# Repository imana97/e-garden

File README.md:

## E-garden

Arduino Shield:

PCB Design:

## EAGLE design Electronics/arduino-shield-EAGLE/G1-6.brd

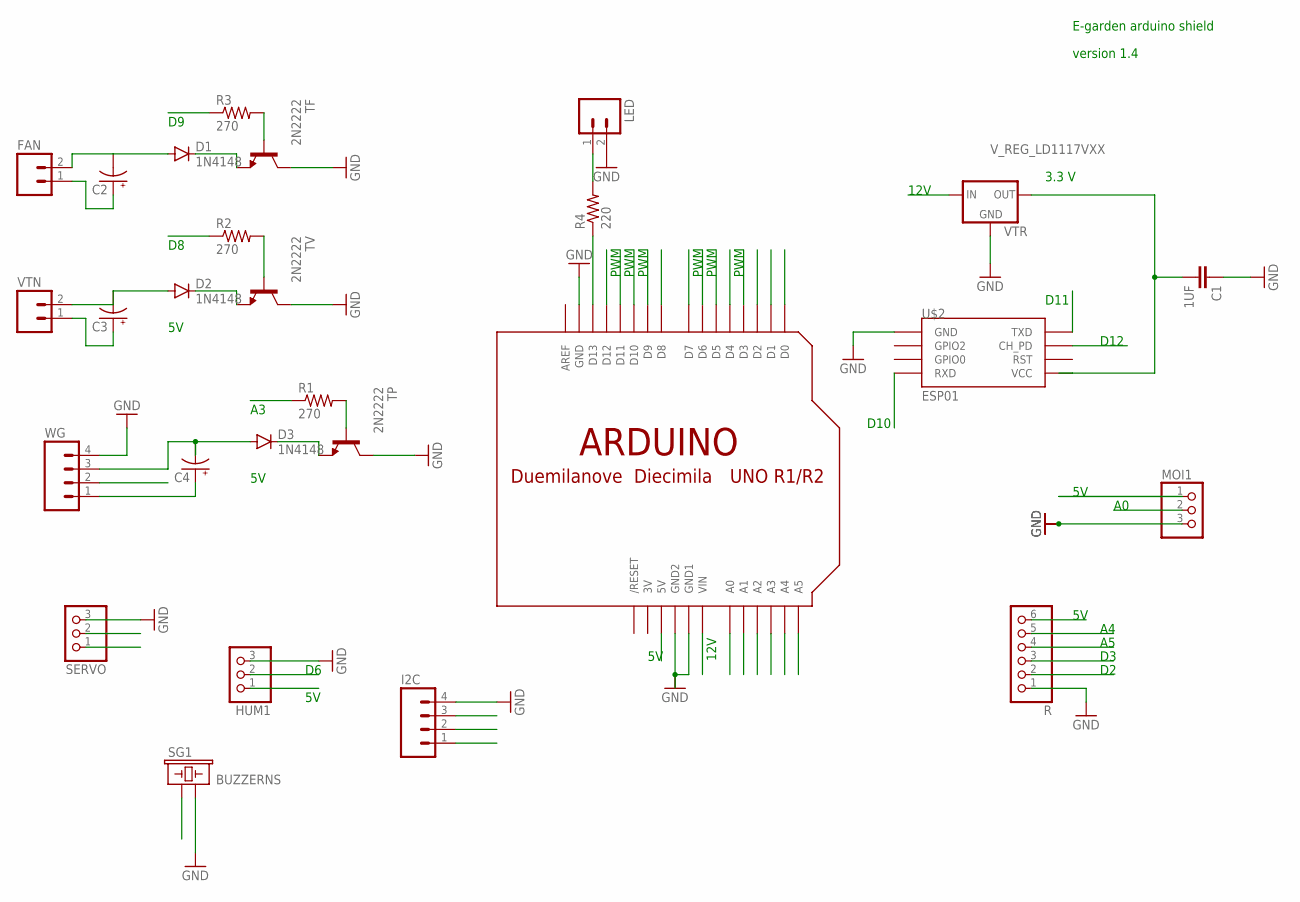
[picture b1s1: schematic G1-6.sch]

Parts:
C1: 1UF; CAP-PTH-SMALL-KIT
C2, C3, C4: CAP_POLPTH2; CPOL-RADIAL-10UF-25V
D1, D2, D3: 1N4148; DIODE-1N4148
FAN: M02PTH; 1X02
HUM1: PINHD-1X3CB; 1X03-CLEANBIG
I2C: M04NO_SILK_ALL_ROUND; 1X04_NO_SILK_ALL_ROUND
LED: M02PTH; 1X02
MOI1: PINHD-1X3CB; 1X03-CLEANBIG
R: PINHD-1X6CB; 1X06-CLEANBIG
R1, R2, R3: 270; AXIAL-0.4
R4: 220; AXIAL-0.4
SERVO: PINHD-1X3CB; 1X03-CLEANBIG
SG1: BUZZERNS; BUZZER-12MM-NS
TF: 2N2222; TO92-EBC-OVAL
TP: 2N2222; TO92-EBC-OVAL
TV: 2N2222; TO92-EBC-OVAL
U$1: ARDUINO-BPLACE
U$2: ESP01
VTN: M02PTH; 1X02
VTR: V_REG_LD1117VXX; 78XXL
WG: M04NO_SILK_ALL_ROUND; 1X04_NO_SILK_ALL_ROUND

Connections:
3V: U$1.3V
A0: MOI1.2, U$1.A0
A1: U$1.A1, WG.2
A2: R.4, U$1.A2
A3: R.5, U$1.A3
A4: I2C.3, U$1.A4
A5: I2C.2, U$1.A5
D0: U$1.D0
D1: U$1.D1
D2: R.3, U$1.D2
D3: R.2, U$1.D3
D4: SERVO.2, U$1.D4
D5: SG1.+ (1), U$1.D5
D6: HUM1.2, U$1.D6
D7: R1.P$1 (1), U$1.D7
D8: R2.P$1 (1), U$1.D8
D9: R3.P$1 (1), U$1.D9
D10: U$1.D10, U$2.RX (RXD)
D11: U$1.D11, U$2.TX (TXD)
D12: U$1.D12, U$2.CH_PD
D13: R4.P$1 (1), U$1.D13
GND: C1.1, HUM1.3, I2C.4, LED.2, MOI1.3, R.1, SERVO.3, SG1.- (2), TF.C, TP.C, TV.C, U$1.GND, U$1.GND1, U$1.GND2, U$2.GND, VTR.IN (GND), WG.4
unnamed: D1.C, TF.E
unnamed: LED.1, R4.P$2 (2)
unnamed: D2.C, TV.E
unnamed: D3.C, TP.E
unnamed: R3.P$2 (2), TF.B
unnamed: C3.2 (-), D2.A, VTN.2
unnamed: R1.P$2 (2), TP.B
unnamed: C1.2, U$2.VCC, VTR.GND (OUT)
unnamed: C2.2 (-), D1.A, FAN.2
unnamed: C4.2 (-), D3.A, WG.3
TV: R2.P$2 (2), TV.B
V5: C2.1 (+), C3.1 (+), C4.1 (+), FAN.1, HUM1.1, I2C.1, MOI1.1, R.6, SERVO.1, U$1.5V, VTN.1, WG.1
V12: U$1.VIN, VTR.OUT (IN)

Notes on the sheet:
12V
3.3 V
D11
D10
D12
E-garden arduino shield
PWM
version 1.4

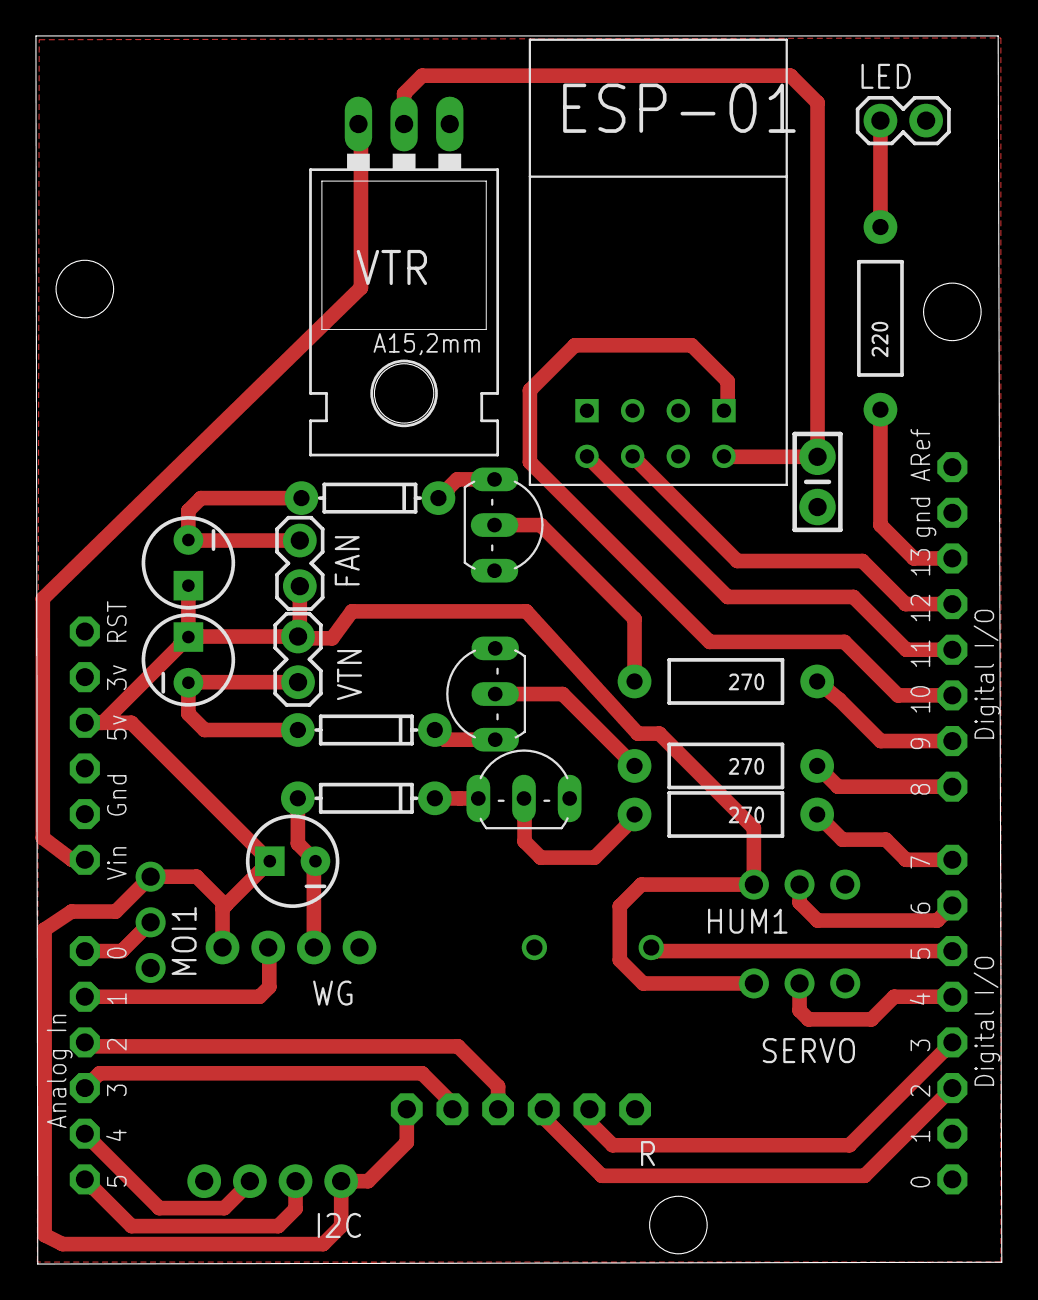
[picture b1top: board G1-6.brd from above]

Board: 2 copper layers, 53.7 x 68.3 mm, 27 parts (0 on the bottom side), 32 nets.

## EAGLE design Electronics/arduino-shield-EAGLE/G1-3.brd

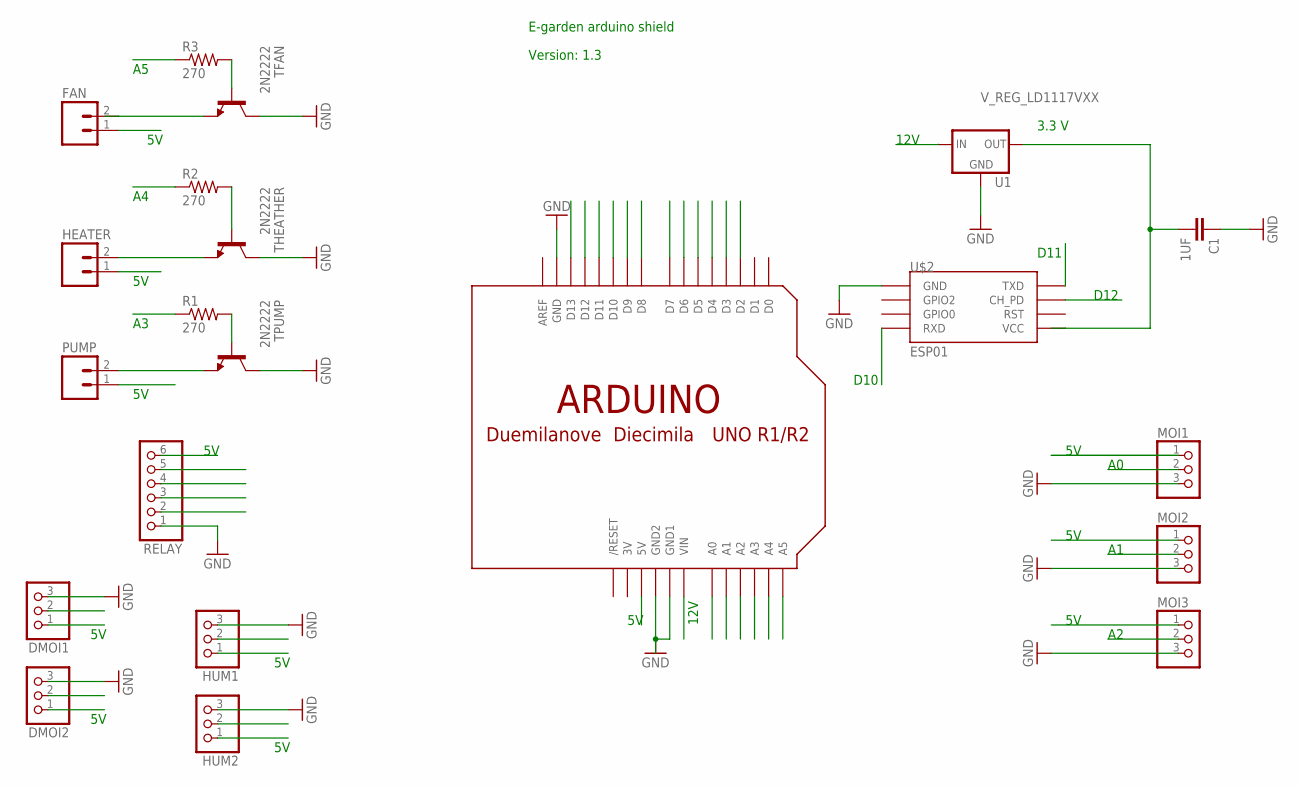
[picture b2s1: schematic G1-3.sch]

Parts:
C1: 1UF; CAP-PTH-SMALL-KIT
DMOI1, DMOI2: PINHD-1X3CB; 1X03-CLEANBIG
FAN: M02PTH; 1X02
HEATER: M02PTH; 1X02
HUM1, HUM2: PINHD-1X3CB; 1X03-CLEANBIG
MOI1, MOI2, MOI3: PINHD-1X3CB; 1X03-CLEANBIG
PUMP: M02PTH; 1X02
R1, R2, R3: 270; AXIAL-0.4
RELAY: PINHD-1X6CB; 1X06-CLEANBIG
TFAN: 2N2222; TO92-EBC-OVAL
THEATHER: 2N2222; TO92-EBC-OVAL
TPUMP: 2N2222; TO92-EBC-OVAL
U1: V_REG_LD1117VXX; 78XXL
U$1: ARDUINO-BPLACE
U$2: ESP01

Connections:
3V: U$1.3V
A0: MOI1.2, U$1.A0
A1: MOI2.2, U$1.A1
A2: MOI3.2, U$1.A2
A3: R1.P$1 (1), U$1.A3
A4: R2.P$1 (1), U$1.A4
A5: R3.P$1 (1), U$1.A5
D2: HUM1.2, U$1.D2
D3: HUM2.2, U$1.D3
D4: DMOI1.2, U$1.D4
D5: DMOI2.2, U$1.D5
D6: RELAY.2, U$1.D6
D7: RELAY.3, U$1.D7
D8: RELAY.4, U$1.D8
D9: RELAY.5, U$1.D9
D10: U$1.D10, U$2.RX (RXD)
D11: U$1.D11, U$2.TX (TXD)
D12: U$1.D12, U$2.CH_PD
D13: U$1.D13
GND: C1.1, DMOI1.3, DMOI2.3, HUM1.3, HUM2.3, MOI1.3, MOI2.3, MOI3.3, RELAY.1, TFAN.C, THEATHER.C, TPUMP.C, U1.IN (GND), U$1.GND, U$1.GND1, U$1.GND2, U$2.GND
unnamed: FAN.2, TFAN.E
unnamed: HEATER.2, THEATHER.E
unnamed: PUMP.2, TPUMP.E
unnamed: R3.P$2 (2), TFAN.B
unnamed: R2.P$2 (2), THEATHER.B
unnamed: R1.P$2 (2), TPUMP.B
unnamed: C1.2, U1.GND (OUT), U$2.VCC
V5: DMOI1.1, DMOI2.1, FAN.1, HEATER.1, HUM1.1, HUM2.1, MOI1.1, MOI2.1, MOI3.1, PUMP.1, RELAY.6, U$1.5V
V12: U1.OUT (IN), U$1.VIN

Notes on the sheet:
12V
3.3 V
D11
D10
D12
E-garden arduino shield
Version: 1.3

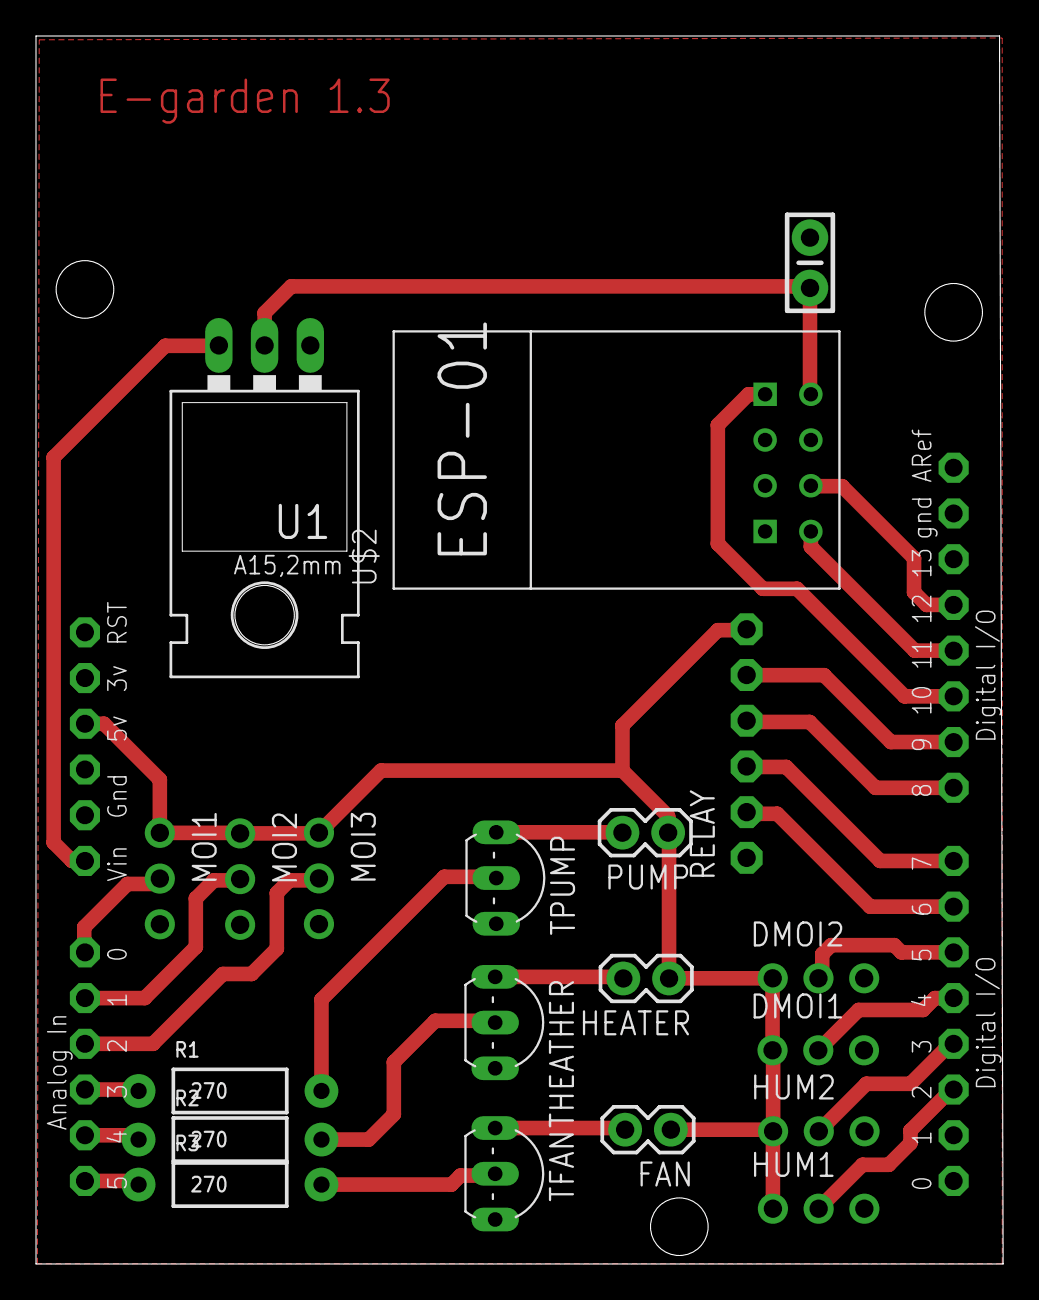
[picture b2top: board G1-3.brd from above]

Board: 2 copper layers, 53.7 x 68.2 mm, 21 parts (0 on the bottom side), 27 nets.

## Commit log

2017-01-03 init
2017-01-11 Set theme jekyll-theme-architect
2017-01-11 board version 1.4
2017-01-11 .DS_Store banished!
2017-01-11 image
2017-01-19 shield version 1.6

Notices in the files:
parts and their libraries:
SparkFun-Capacitors: Licensing: Creative Commons ShareAlike 4.0 International - https://creativecommons.org/licenses/by-sa/4.0
